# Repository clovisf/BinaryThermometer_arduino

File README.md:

BinaryThermometer_arduino
=========================

Arduino code for my first project, a binary thermometer

Please refer to my blog for further information: 
http://embedded-clovis.blogspot.ca/

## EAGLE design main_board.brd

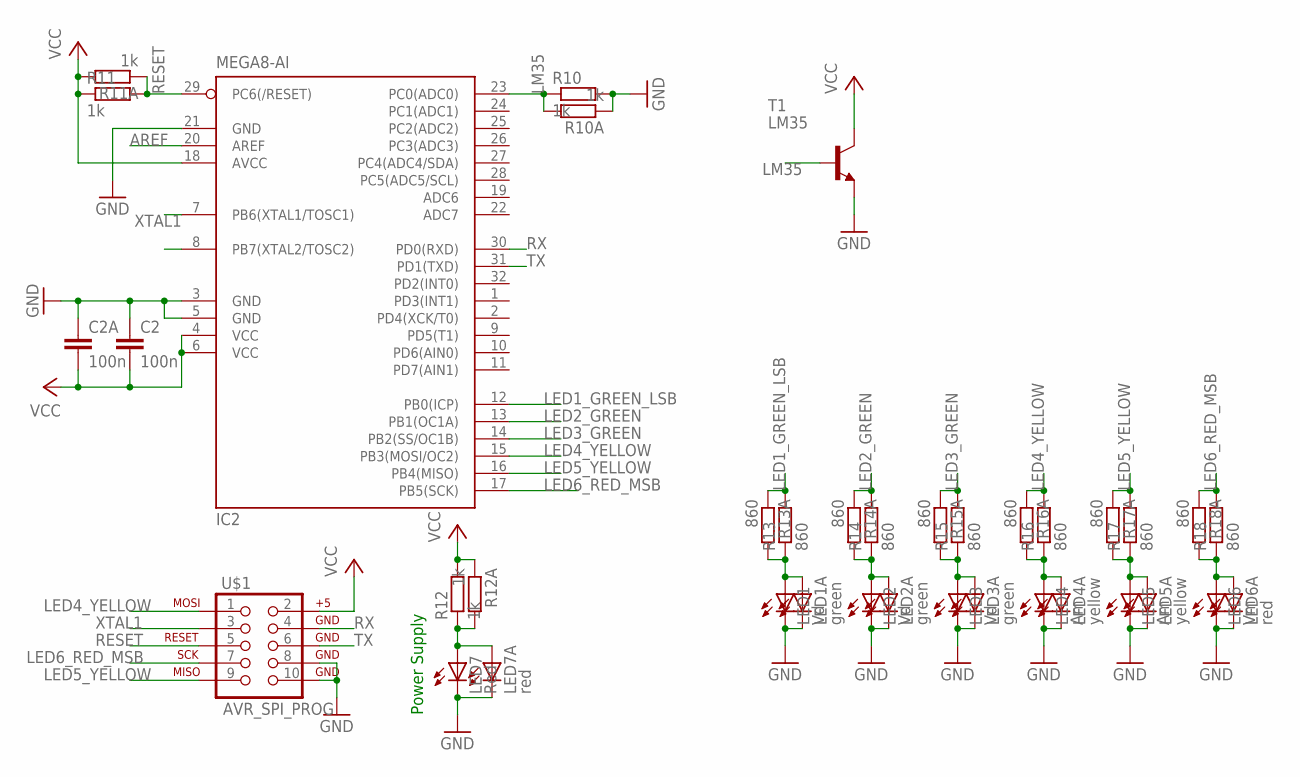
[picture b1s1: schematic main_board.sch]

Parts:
C2: 100n; C5B3
C2A: 100n; C0805
IC2: MEGA8-AI; TQFP32-08
LED1, LED2, LED3: Vd; LED3MM
LED1A, LED2A, LED3A: green; CHIP-LED0805
LED4, LED5: Am; LED3MM
LED4A, LED5A: yellow; CHIP-LED0805
LED6: Vm; LED3MM
LED6A, LED7A: red; CHIP-LED0805
LED7: Red; LED3MM
R10, R11, R12: 1k; 0207/10
R10A, R11A, R12A: 1k; M0805
R13, R14, R15, R16, R17, R18: 860; 0207/10
R13A, R14A, R15A, R16A, R17A, R18A: 860; M0805
T1: LM35; TO92-CBE
U$1: AVR_SPI_PROG; AVR_ICSP

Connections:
AREF: IC2.20 (AREF)
GND: C2.1, C2A.1, IC2.3 (GND), IC2.5 (GND), IC2.21 (GND), LED1.K (C), LED1A.C, LED2.K (C), LED2A.C, LED3.K (C), LED3A.C, LED4.K (C), LED4A.C, LED5.K (C), LED5A.C, LED6.K (C), LED6A.C, LED7.K (C), LED7A.C, R10.2, R10A.1, T1.E, U$1.8, U$1.10
LED1_GREEN_LSB: IC2.12 (PB0(ICP)), R13.2, R13A.1
LED2_GREEN: IC2.13 (PB1(OC1A)), R14.2, R14A.1
LED3_GREEN: IC2.14 (PB2(SS/OC1B)), R15.2, R15A.1
LED4_YELLOW: IC2.15 (PB3(MOSI/OC2)), R16.2, R16A.1, U$1.1
LED5_YELLOW: IC2.16 (PB4(MISO)), R17.2, R17A.1, U$1.9
LED6_RED_MSB: IC2.17 (PB5(SCK)), R18.2, R18A.1, U$1.7
LM35: IC2.23 (PC0(ADC0)), R10.1, R10A.2, T1.B
unnamed: LED1.A, LED1A.A, R13.1, R13A.2
unnamed: LED2.A, LED2A.A, R14.1, R14A.2
unnamed: LED7.A, LED7A.A, R12.1, R12A.2
unnamed: LED3.A, LED3A.A, R15.1, R15A.2
unnamed: LED4.A, LED4A.A, R16.1, R16A.2
unnamed: LED5.A, LED5A.A, R17.1, R17A.2
unnamed: LED6.A, LED6A.A, R18.1, R18A.2
RESET: IC2.29 (PC6(/RESET)), R11.2, R11A.1, U$1.5
RX: IC2.30 (PD0(RXD)), U$1.4
TX: IC2.31 (PD1(TXD)), U$1.6
VCC: C2.2, C2A.2, IC2.4 (VCC), IC2.6 (VCC), IC2.18 (AVCC), R11.1, R11A.2, R12.2, R12A.1, T1.C, U$1.2
XTAL1: IC2.7 (PB6(XTAL1/TOSC1)), U$1.3

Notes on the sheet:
Power Supply

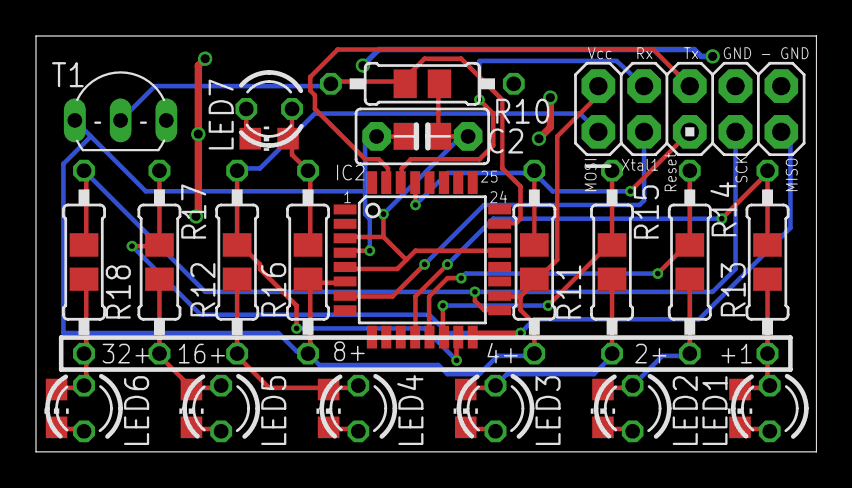
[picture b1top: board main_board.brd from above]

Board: 2 copper layers, 43.4 x 23.1 mm, 37 parts (0 on the bottom side), 20 nets.

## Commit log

2014-06-18 initial release
2016-03-07 Main revison of concept and sketchs
    This is a revison that includes PCB modifications (made it optional both
    SMD and TH components) and software corrections.

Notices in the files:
parts and their libraries:
SparkFun-Connectors: Licensing: Creative Commons ShareAlike 4.0 International - https://creativecommons.org/licenses/by-sa/4.0
